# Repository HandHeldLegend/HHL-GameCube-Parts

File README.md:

# HHL-GameCube-Parts

3D Printable GameCube controller parts.

Do whatever you want with the files according to the license. 
Keep these parts open and available for anyone to use.

Mold them, print them, sell them, we don't care. Just provide attribution and retain the same license for derivatives.

## Attributions
Ergo trigger profiles modelled after work from [Mikey](https://twitter.com/yaboimikey97) with permission provided.

Controller shell is, in large part, modelled using great reference scans provided by [Wesk on BitBuilt](https://bitbuilt.net/forums/index.php?threads/gamecube-oem-controller-scan.3844/).

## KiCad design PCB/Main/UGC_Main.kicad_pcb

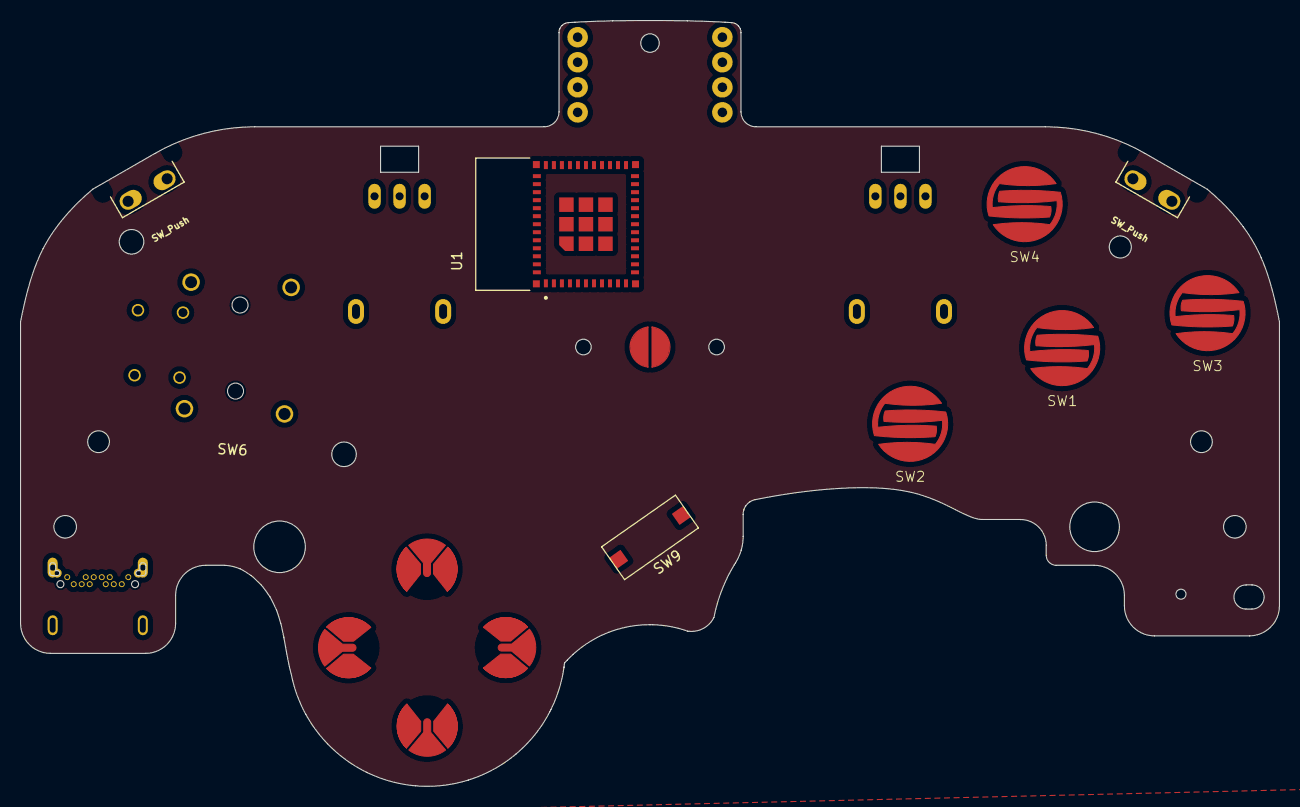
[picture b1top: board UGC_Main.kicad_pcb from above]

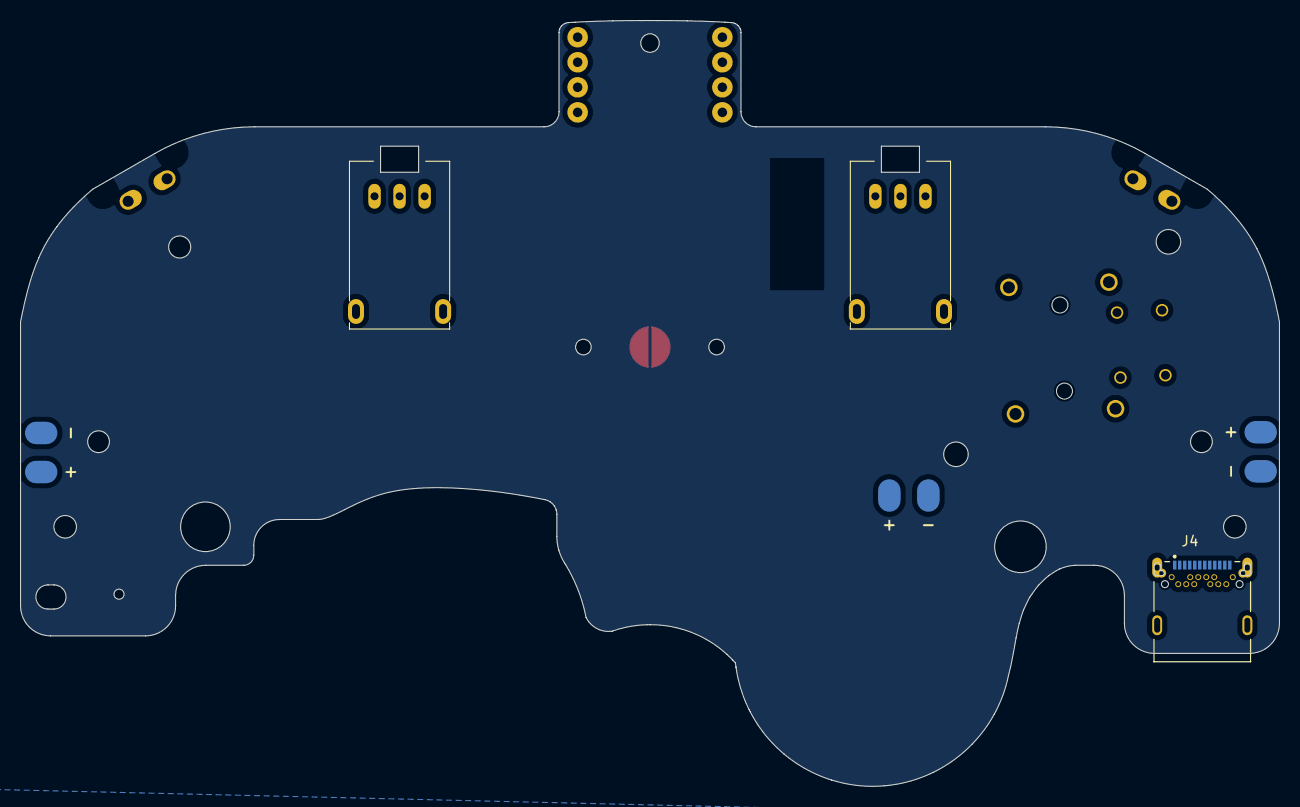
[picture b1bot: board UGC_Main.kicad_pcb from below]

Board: 2 copper layers, 125.7 x 76.4 mm, 28 parts (6 on the bottom side), 4 nets, no tracks yet.

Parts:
J1: Rumble; rumble_pins
J2: LT; rumble_pins
J3: RT; rumble_pins
J4: UJ31-CH-G1-SMT-TR; CUI_UJ31-CH-G1-SMT-TR
J5, J6, J7, J8, J9, J10, J11, J12: Conn_01x01_Pin; YZ72015053P-01
RV1, RV2: Slider_GCC-Gamecube_MB; GCC_Slider
SW1, SW2, SW3, SW4: SW_Push; progcc_bpad
SW5: SW_Push; snes_pad
SW6: GL18_SW; GL18
SW7, SW8: SW_Push; Z_Switch_Edge_Omron
SW9: TS09-63-25-R-260-SMT; TS09
SW10, SW11, SW12, SW13: SW_Push; progcc_dpad
U1: ESP32-PICO-MINI-02; MODULE_ESP32-PICO-MINI-02

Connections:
unnamed: J4.A1 (GND), J4.A12 (GND), J4.B1 (GND), J4.B12 (GND)
unnamed: J4.SH1 (SHIELD), J4.SH2 (SHIELD), J4.SH3 (SHIELD), J4.SH4 (SHIELD), J4.SH5 (SHIELD), J4.SH6 (SHIELD)
unnamed: J4.A4 (VBUS), J4.A9 (VBUS), J4.B4 (VBUS), J4.B9 (VBUS)
unnamed: U1.1 (GND), U1.2 (GND), U1.11 (GND), U1.14 (GND), U1.36 (GND), U1.37 (GND), U1.38 (GND), U1.39 (GND), U1.40 (GND), U1.41 (GND), U1.42 (GND), U1.43 (GND), U1.44 (GND), U1.45 (GND), U1.46 (GND), U1.47 (GND), U1.48 (GND), U1.49 (GND), U1.50 (GND), U1.51 (GND), U1.52 (GND), U1.53 (GND), U1.54 (GND), U1.55 (GND), U1.56 (GND), U1.57 (GND), U1.58 (GND), U1.59 (GND), U1.60 (GND), U1.61 (GND)

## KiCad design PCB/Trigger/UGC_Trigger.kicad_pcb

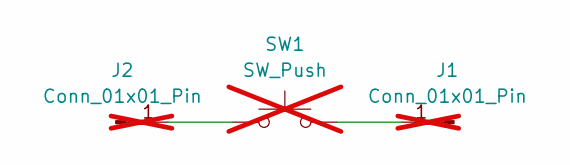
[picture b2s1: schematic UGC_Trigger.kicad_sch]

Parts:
J1, J2: Conn_01x01_Pin; PinHeader_1x01_P2.00mm_Vertical; not fitted
SW1: SW_Push; progcc_bpad; not fitted

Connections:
unnamed: J1.1, SW1.2
unnamed: J2.1, SW1.1

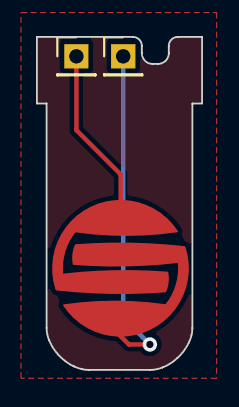
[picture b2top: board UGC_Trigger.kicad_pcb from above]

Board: 2 copper layers, 9.2 x 18.5 mm, 3 parts (0 on the bottom side), 2 nets.

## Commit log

2023-01-19 Attribution added
2023-01-19 Add Z Button
2023-01-19 Update trigger size
    slightly larger (0.3%)
2023-01-20 Add A button
2023-01-20 Add B button
2023-01-24 Remove balds for now, redo OEM
    buttons are more accurate than ever with external dimensions.
2023-01-25 Added d-pad and start buttons.
2023-01-30 Removed faulty ergo filled trigger, add new trigger
2023-01-30 Adjust stem taper dimension
2023-02-25 Adjusted ergo triggers and Dpad
    Fixed an issue with ergo triggers where they wouldn't click. The stem needed to be extended by 1.3mm to actuate the button
2023-02-25 One final trigger update
    Increase depth inside to match OEM
2023-03-12 Increase width of spring wells
2023-04-09 Updated stem inner/outer dimensions
2023-06-28 Resolve bad stitching on A button
2023-11-09 GC Shell Update
2023-11-09 Update pcb lib
2023-11-09 Update attributions
2023-11-11 Shell update
2023-12-01 Update shell and PCB
2023-12-02 Restitch
    Restitch files and add STL shell
2023-12-14 Update
    - Increase face button thickness 0.25mm
    - Increase diameter of press-fit threaded inserts
    - Add battery wire cutout
    - Add battery connector cutout for trigger bracket
2023-12-15 Remove unused
2023-12-15 Increase button top thickness
    0.25mm -> 0.5mm
2023-12-22 Add updated plasticity files
2024-02-06 Update shell and gateplates
    - Add blank gate plate
    - Remove feature for USB-C sub-board (inconsistent connections)
2024-02-07 Few more changes
    - Adjust lower shell to have better trigger stops
    - Adjust trigger bracket for trigger stops
    - Adjust height on analog stick interfacing posts
2024-02-07 Few more changes
    - Adjust lower shell to have better trigger stops
    - Adjust trigger bracket for trigger stops
    - Adjust height on analog stick interfacing posts
    - Update trigger membrane holder to allow proper trigger press distance
2024-02-07 Add more stl
    gate plate stls
2024-03-02 Add new variations
    - Introduce triggers with a slider mechanism (Will probably be gone soon, did not work well)
    - Split Dpad design (Untested)
2024-03-06 Update and restructure
2024-03-12 Update screw hole sizes and insert hole size
